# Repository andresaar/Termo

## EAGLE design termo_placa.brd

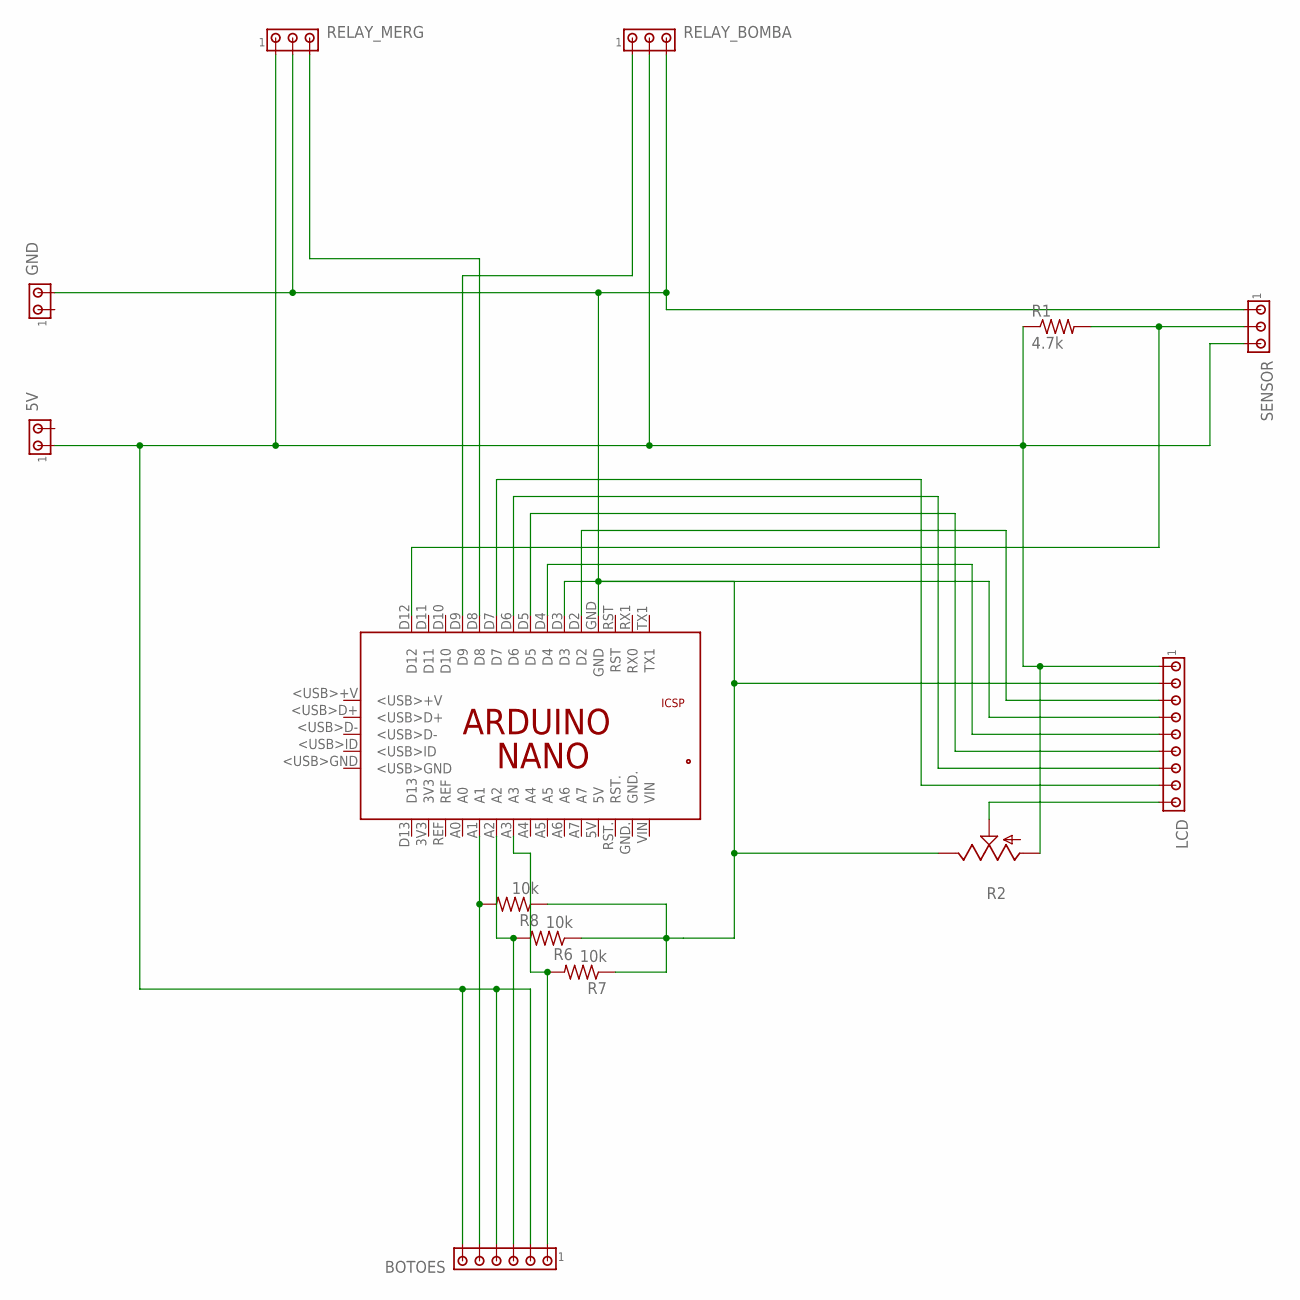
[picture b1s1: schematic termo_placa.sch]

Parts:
5V: MTA02-156; 1X2MTA
BOTOES: MTA06-156; 1X6MTA
GND: MTA02-156; 1X2MTA
LCD: MTA09-156; 1X9MTA
PCB1: ARDUINO_NANO
R1: 4.7k; 0204/7
R2: TRIM_US-CA9V; CA9V
R6, R7, R8: 10k; 0204/7
RELAY_BOMBA: MTA03-156; 1X3MTA
RELAY_MERG: MTA03-156; 1X3MTA
SENSOR: MTA03-100; 10X03MTA

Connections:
unnamed: GND.2, LCD.2, PCB1.GND, R2.E, R6.1, R7.1, RELAY_BOMBA.3, RELAY_MERG.2, SENSOR.1
unnamed: 5V.1, BOTOES.2, BOTOES.4, BOTOES.6, LCD.1, R1.1, R2.A, RELAY_BOMBA.2, RELAY_MERG.1, SENSOR.3
unnamed: PCB1.D8, RELAY_MERG.3
unnamed: PCB1.D9, RELAY_BOMBA.1
unnamed: BOTOES.5, PCB1.A1, R8.2
unnamed: PCB1.D12, R1.2, SENSOR.2
unnamed: BOTOES.3, PCB1.A2, R6.2
unnamed: BOTOES.1, PCB1.A3, R7.2
unnamed: LCD.3, PCB1.D2
unnamed: LCD.4, PCB1.D3
unnamed: LCD.5, PCB1.D4
unnamed: LCD.6, PCB1.D5
unnamed: LCD.7, PCB1.D6
unnamed: LCD.8, PCB1.D7
unnamed: LCD.9, R2.S

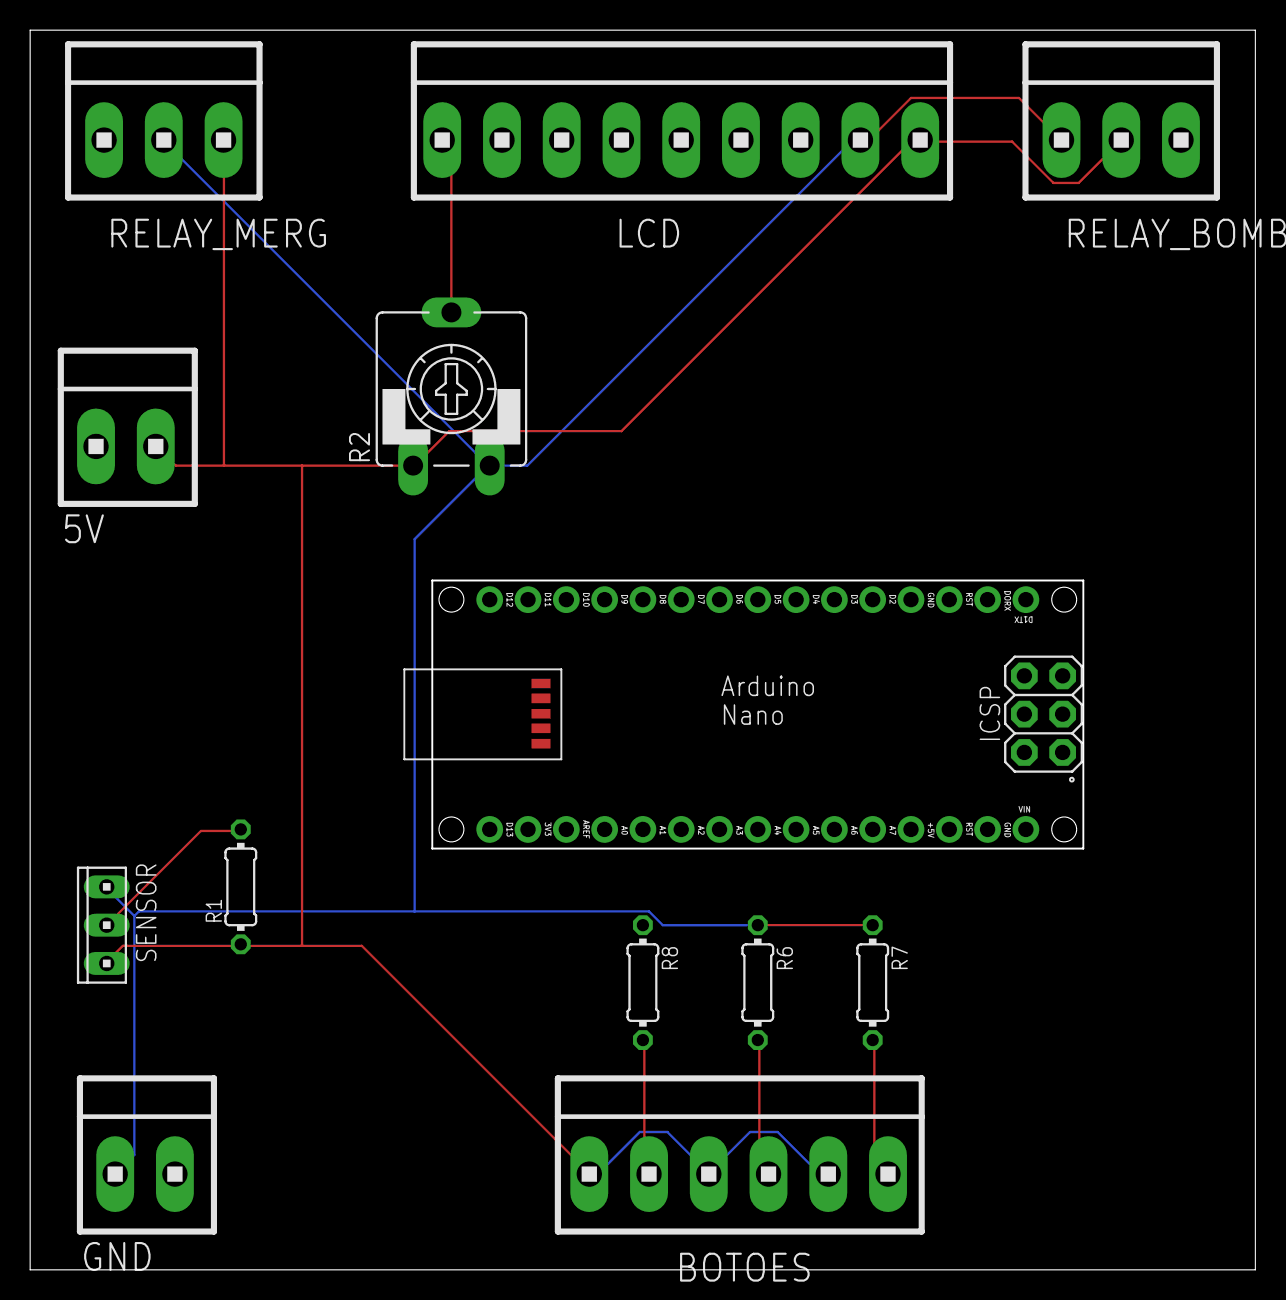
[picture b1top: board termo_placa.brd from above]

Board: 2 copper layers, 81.1 x 82.1 mm, 13 parts (0 on the bottom side), 15 nets.

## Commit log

2017-10-31 mais
